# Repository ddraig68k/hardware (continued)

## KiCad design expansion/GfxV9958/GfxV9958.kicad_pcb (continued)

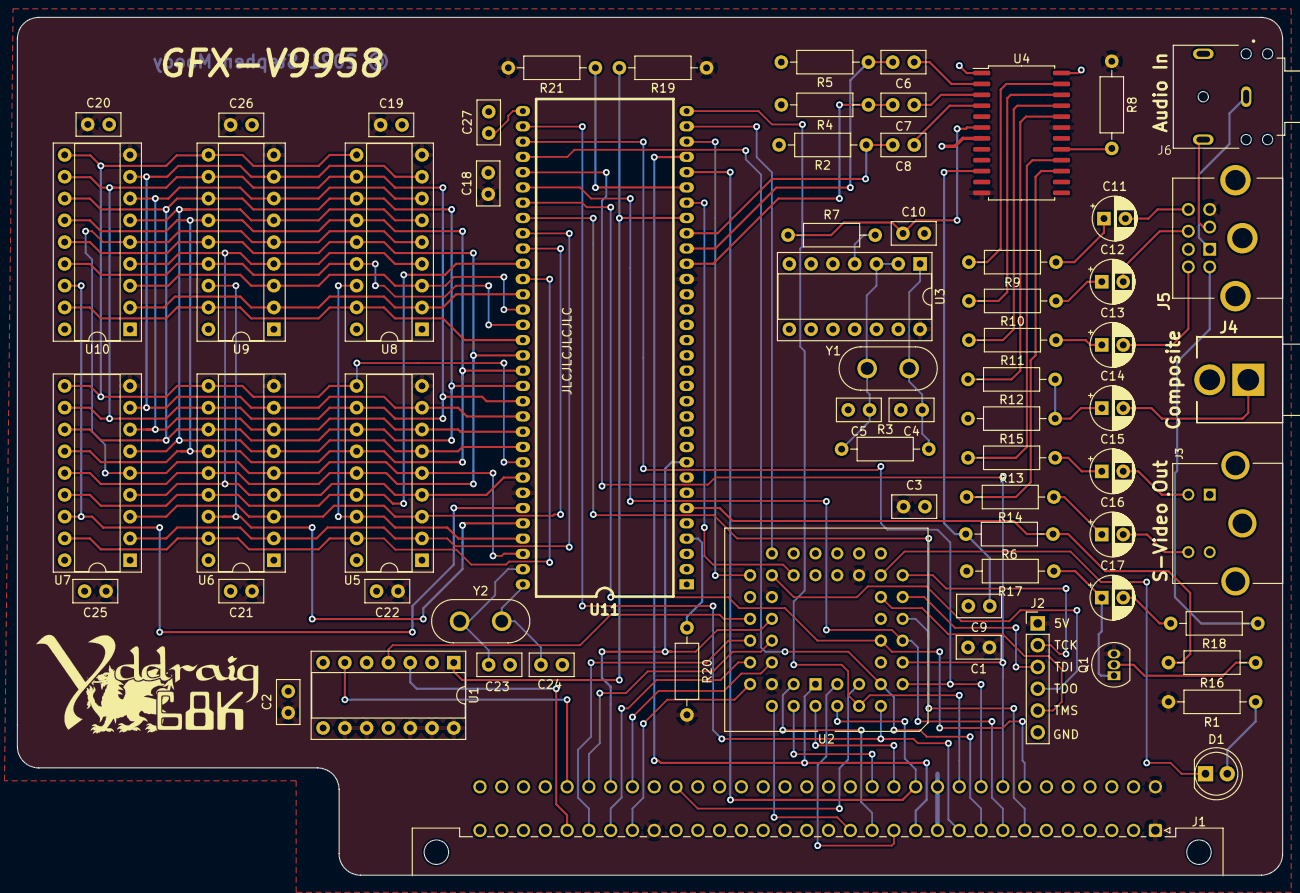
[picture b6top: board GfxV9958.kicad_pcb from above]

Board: 2 copper layers, 147.5 x 100.0 mm, 69 parts (0 on the bottom side), 100 nets.

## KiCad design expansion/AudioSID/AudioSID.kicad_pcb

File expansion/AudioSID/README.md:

# Dual SID Audio Card

The [MOS 6581/8580 SID](https://en.wikipedia.org/wiki/MOS_Technology_SID) is the sound chip used in the Commodore 64, with 3 independent oscillators, multiple waveforms, ADSR envelopes and a multi-mode filter giving it its distinctive sound.

This card has two SID sockets, each jumper-selectable between the original 6581 and the later 8580 variant, since the two chips have different characteristics - the 8580 cleaned up some of the 6581's non-linearities and runs from a 9V analog supply rather than the 6581's 12V. The board provides both rails, with an L7809 regulator supplying the 9V needed by the 8580.

A Xilinx XC9536PC44 CPLD handles address decoding and chip select generation for both SID sockets. Each SID has its own volume potentiometer for mixing before the two channels are combined into a single audio output, with a separate analog supply and ground plane to help keep noise out of the signal.

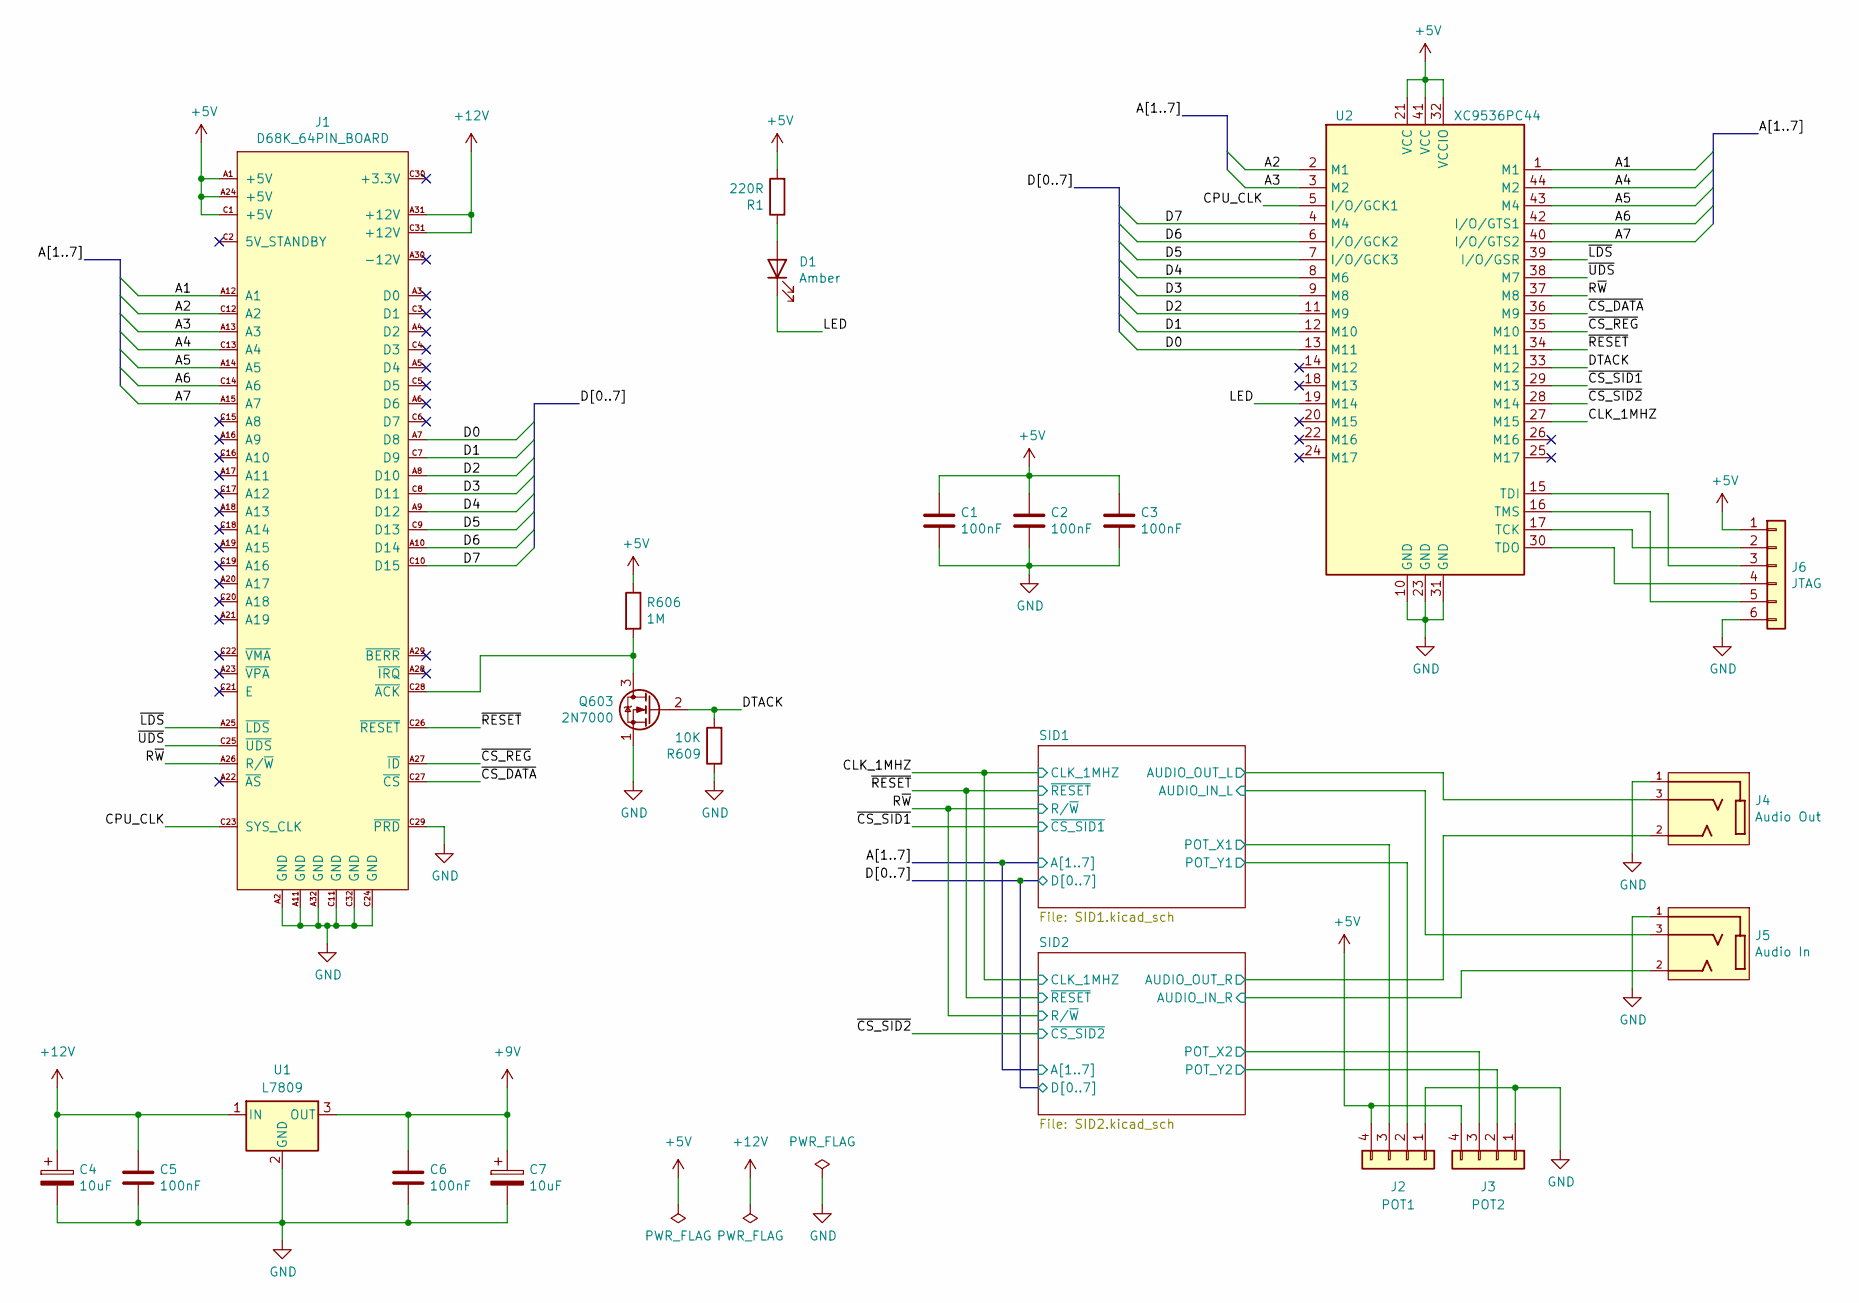
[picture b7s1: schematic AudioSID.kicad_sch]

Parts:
C1, C2, C3, C5, C6: 100nF; C_Disc_D5.0mm_W2.5mm_P2.50mm
C4, C7: 10uF; CP_Radial_D5.0mm_P2.50mm
D1: Amber; LED_D5.0mm
J1: D68K_64PIN_BOARD; DIN41612_C_2x32_Male_Horizontal_THT
J2: POT1; PinHeader_1x04_P2.54mm_Vertical
J3: POT2; PinHeader_1x04_P2.54mm_Vertical
J4: Audio Out; SWITCHCRAFT_35RAPC2BHN2; PARTREV L
J5: Audio In; SWITCHCRAFT_35RAPC2BHN2; PARTREV L
J6: JTAG; PinHeader_1x06_P2.54mm_Vertical
Q603: 2N7000; TO-92_Inline
R1: 220R; R_Axial_DIN0207_L6.3mm_D2.5mm_P10.16mm_Horizontal
R606: 1M; R_Axial_DIN0207_L6.3mm_D2.5mm_P10.16mm_Horizontal
R609: 10K; R_Axial_DIN0207_L6.3mm_D2.5mm_P10.16mm_Horizontal
U1: L7809; TO-220-3_Horizontal_TabDown
U2: XC9536PC44; PLCC-44_THT-Socket

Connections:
/A1: J1.A12 (A1), U2.1 (M1); also elsewhere on the board
/A2: J1.C12 (A2), U2.2 (M1); also elsewhere on the board
/A3: J1.A13 (A3), U2.3 (M2); also elsewhere on the board
/A4: J1.C13 (A4), U2.44 (M2); also elsewhere on the board
/A5: J1.A14 (A5), U2.43 (M4); also elsewhere on the board
/A6: J1.C14 (A6), U2.42 (I/O/GTS1)
/A7: J1.A15 (A7), U2.40 (I/O/GTS2)
/CLK_1MHZ: U2.27 (M15); also elsewhere on the board
/CPU_CLK: J1.C23 (SYS_CLK), U2.5 (I/O/GCK1)
/D0: J1.A7 (D8), U2.13 (M11); also elsewhere on the board
/D1: J1.C7 (D9), U2.12 (M10); also elsewhere on the board
/D2: J1.A8 (D10), U2.11 (M9); also elsewhere on the board
/D3: J1.C8 (D11), U2.9 (M8); also elsewhere on the board
/D4: J1.A9 (D12), U2.8 (M6); also elsewhere on the board
/D5: J1.C9 (D13), U2.7 (I/O/GCK3); also elsewhere on the board
/D6: J1.A10 (D14), U2.6 (I/O/GCK2); also elsewhere on the board
/D7: J1.C10 (D15), U2.4 (M4); also elsewhere on the board
/DTACK: U2.33 (M12); also elsewhere on the board
/LED: D1.1 (K), U2.19 (M14)
/R~W: J1.A26 (R/~W), U2.37 (M8); also elsewhere on the board
/SID1/AUDIO_IN_L: J5.3; also elsewhere on the board
/SID1/AUDIO_OUT_L: J4.3; also elsewhere on the board
/SID1/POT_Y1: J2.2; also elsewhere on the board
/SID2/AUDIO_IN_R: J5.2; also elsewhere on the board
/SID2/AUDIO_OUT_R: J4.2; also elsewhere on the board
/SID2/POT_X2: J3.3; also elsewhere on the board
/SID2/POT_Y2: J3.2; also elsewhere on the board
/~CS_DATA: J1.C27 (~CS), U2.36 (M9)
/~CS_REG: J1.A27 (~ID), U2.35 (M10)
/~CS_SID1: U2.29 (M13); also elsewhere on the board
/~CS_SID2: U2.28 (M14); also elsewhere on the board
/~LDS: J1.A25 (~LDS), U2.39 (I/O/GSR)
/~RESET: J1.C26 (~RESET), U2.34 (M11); also elsewhere on the board
/~UDS: J1.C25 (~UDS), U2.38 (M7)
GND: C1.2, C2.2, C3.2, C4.2, C5.2, C6.2, C7.2, J1.A2 (GND), J1.A11 (GND), J1.A32 (GND), J1.C11 (GND), J1.C24 (GND), J1.C29 (~PRD), J1.C32 (GND), J2.1, J3.1, J4.1, J5.1, J6.6, U1.2 (GND), U2.10 (GND), U2.23 (GND), U2.31 (GND); also elsewhere on the board
unnamed: D1.2 (A), R1.1
unnamed 36: J1.C28 (~ACK); also elsewhere on the board
unnamed: J6.2, U2.17 (TCK)
unnamed: J6.3, U2.15 (TDI)
unnamed: J6.4, U2.30 (TDO)
unnamed: J6.5, U2.16 (TMS)

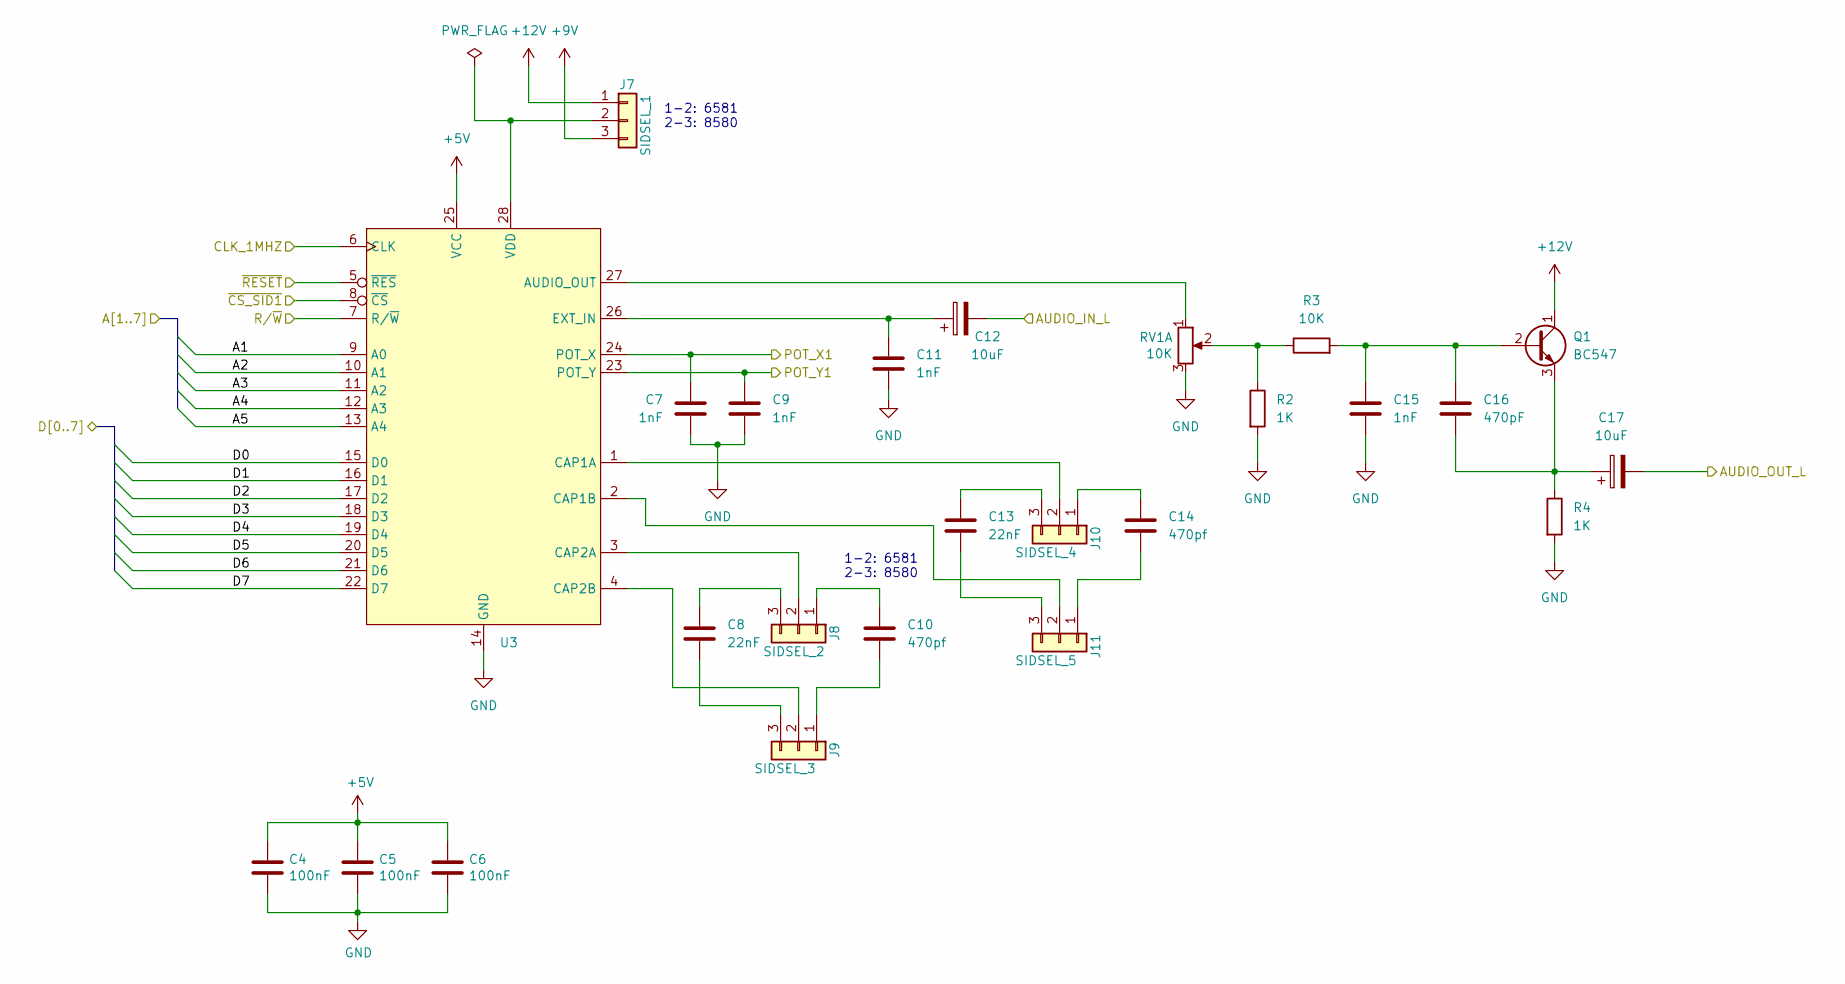
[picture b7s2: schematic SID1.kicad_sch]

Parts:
C4, C5, C6: 100nF; C_Disc_D5.0mm_W2.5mm_P2.50mm
C7, C9, C11, C15: 1nF; C_Disc_D5.0mm_W2.5mm_P2.50mm
C8, C13: 22nF; C_Disc_D5.0mm_W2.5mm_P2.50mm
C10, C14: 470pf; C_Disc_D5.0mm_W2.5mm_P2.50mm
C12, C17: 10uF; CP_Radial_D5.0mm_P2.50mm
C16: 470pF; C_Disc_D5.0mm_W2.5mm_P2.50mm
J7: SIDSEL_1; PinHeader_1x03_P2.54mm_Vertical
J8: SIDSEL_2; PinHeader_1x03_P2.54mm_Vertical
J9: SIDSEL_3; PinHeader_1x03_P2.54mm_Vertical
J10: SIDSEL_4; PinHeader_1x03_P2.54mm_Vertical
J11: SIDSEL_5; PinHeader_1x03_P2.54mm_Vertical
Q1: BC547; TO-92_Inline
R2, R4: 1K; R_Axial_DIN0207_L6.3mm_D2.5mm_P10.16mm_Horizontal
R3: 10K; R_Axial_DIN0207_L6.3mm_D2.5mm_P10.16mm_Horizontal
RV1: 10K; Potentiometer_Alps_RK163_Dual_Horizontal
U3: DIP-28_W15.24mm_Socket

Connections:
/A1: U3.9 (A0); also elsewhere on the board
/A2: U3.10 (A1); also elsewhere on the board
/A3: U3.11 (A2); also elsewhere on the board
/A4: U3.12 (A3); also elsewhere on the board
/A5: U3.13 (A4); also elsewhere on the board
/CLK_1MHZ: U3.6 (CLK); also elsewhere on the board
/D0: U3.15 (D0); also elsewhere on the board
/D1: U3.16 (D1); also elsewhere on the board
/D2: U3.17 (D2); also elsewhere on the board
/D3: U3.18 (D3); also elsewhere on the board
/D4: U3.19 (D4); also elsewhere on the board
/D5: U3.20 (D5); also elsewhere on the board
/D6: U3.21 (D6); also elsewhere on the board
/D7: U3.22 (D7); also elsewhere on the board
/R~W: U3.7 (R/~W); also elsewhere on the board
/SID1/AUDIO_IN_L: C12.2; also elsewhere on the board
/SID1/AUDIO_OUT_L: C17.2; also elsewhere on the board
/SID1/POT_Y1: C9.1, U3.23 (POT_Y); also elsewhere on the board
/~CS_SID1: U3.8 (~CS); also elsewhere on the board
/~RESET: U3.5 (~RES); also elsewhere on the board
GND: C4.2, C5.2, C6.2, C7.2, C9.2, C11.2, C15.2, R2.2, R4.2, RV1.3, U3.14 (GND); also elsewhere on the board
unnamed: J7.2, U3.28 (VDD)
unnamed: C10.1, J8.1
unnamed: J8.2, U3.3 (CAP2A)
unnamed: C8.1, J8.3
unnamed: C10.2, J9.1
unnamed: J9.2, U3.4 (CAP2B)
unnamed: C8.2, J9.3
unnamed: C14.1, J10.1
unnamed: J10.2, U3.1 (CAP1A)
unnamed: C13.1, J10.3
unnamed: C14.2, J11.1
unnamed: J11.2, U3.2 (CAP1B)
unnamed: C13.2, J11.3
unnamed: C15.1, C16.1, Q1.2 (B), R3.2
unnamed: C16.2, C17.1, Q1.3 (E), R4.1
unnamed: R2.1, R3.1, RV1.2
unnamed: RV1.1, U3.27 (AUDIO_OUT)
unnamed: C11.1, C12.1, U3.26 (EXT_IN)

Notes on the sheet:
1-2: 6581 2-3: 8580

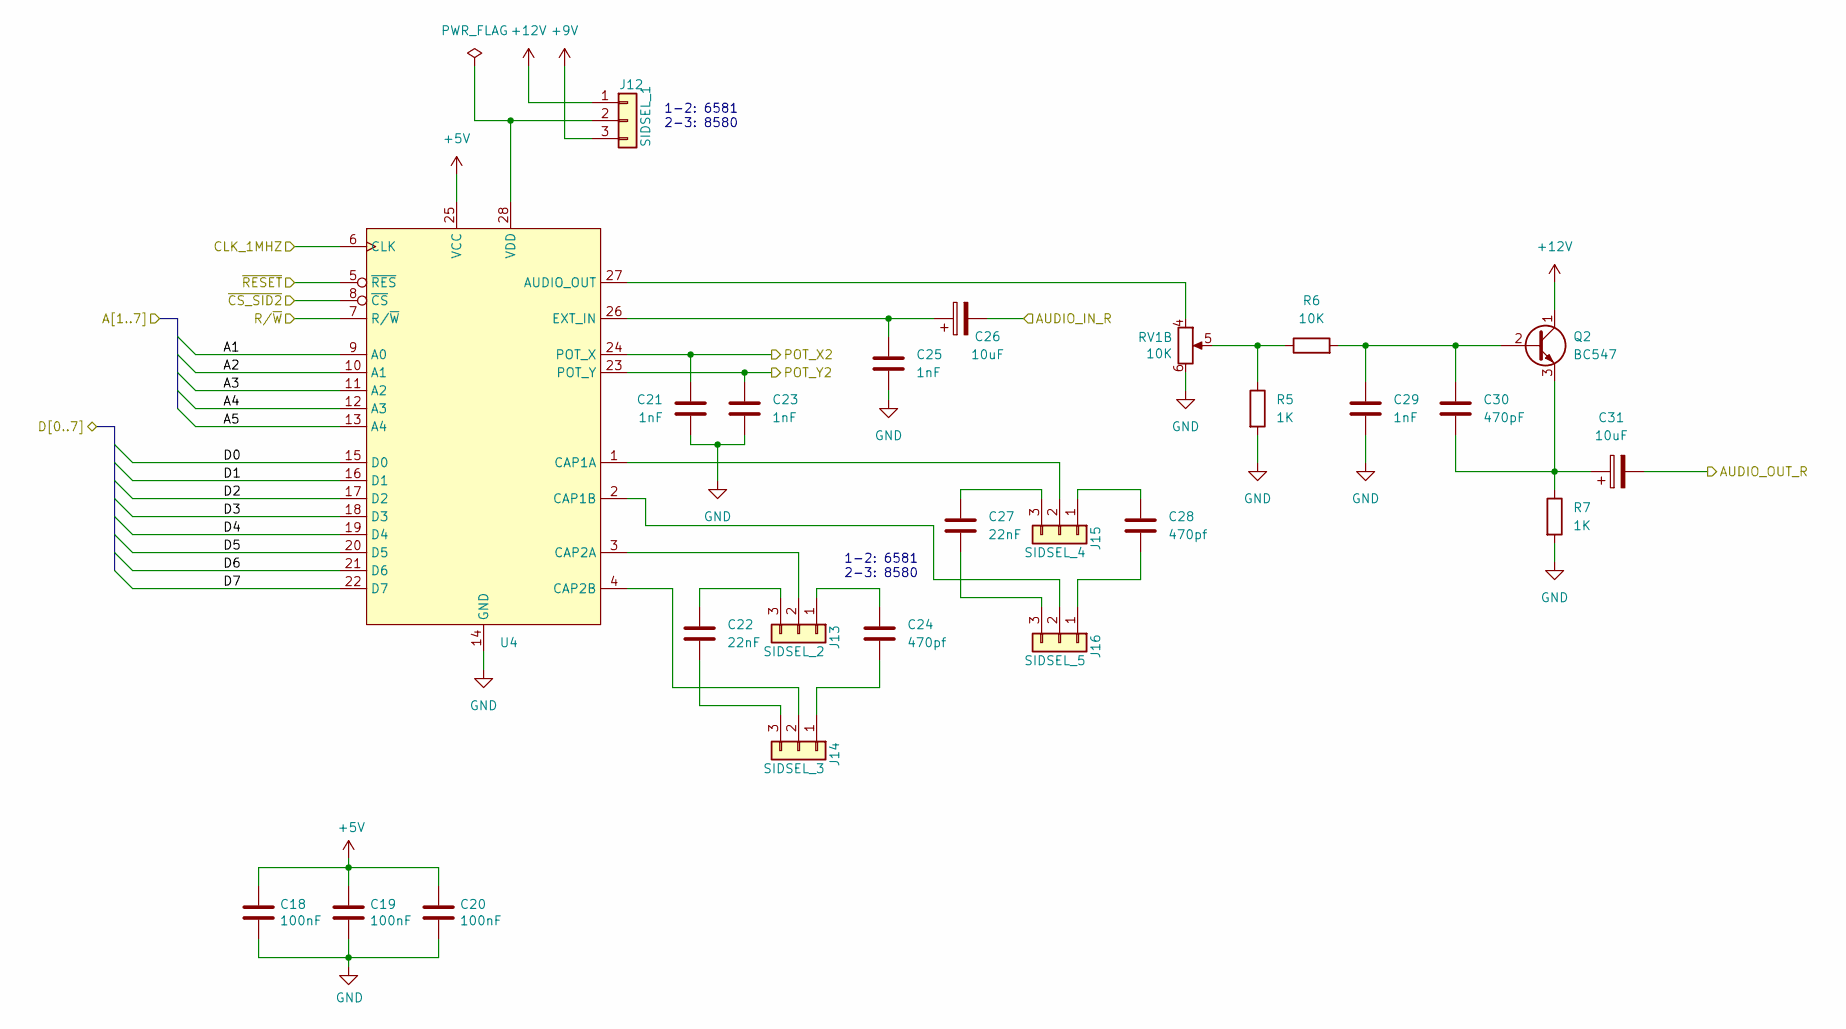
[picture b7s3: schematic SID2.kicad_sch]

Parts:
C18, C19, C20: 100nF; C_Disc_D5.0mm_W2.5mm_P2.50mm
C21, C23, C25, C29: 1nF; C_Disc_D5.0mm_W2.5mm_P2.50mm
C22, C27: 22nF; C_Disc_D5.0mm_W2.5mm_P2.50mm
C24, C28: 470pf; C_Disc_D5.0mm_W2.5mm_P2.50mm
C26, C31: 10uF; CP_Radial_D5.0mm_P2.50mm
C30: 470pF; C_Disc_D5.0mm_W2.5mm_P2.50mm
J12: SIDSEL_1; PinHeader_1x03_P2.54mm_Vertical
J13: SIDSEL_2; PinHeader_1x03_P2.54mm_Vertical
J14: SIDSEL_3; PinHeader_1x03_P2.54mm_Vertical
J15: SIDSEL_4; PinHeader_1x03_P2.54mm_Vertical
J16: SIDSEL_5; PinHeader_1x03_P2.54mm_Vertical
Q2: BC547; TO-92_Inline
R5, R7: 1K; R_Axial_DIN0207_L6.3mm_D2.5mm_P10.16mm_Horizontal
R6: 10K; R_Axial_DIN0207_L6.3mm_D2.5mm_P10.16mm_Horizontal
RV1: 10K; Potentiometer_Alps_RK163_Dual_Horizontal
U4: DIP-28_W15.24mm_Socket

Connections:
/A1: U4.9 (A0); also elsewhere on the board
/A2: U4.10 (A1); also elsewhere on the board
/A3: U4.11 (A2); also elsewhere on the board
/A4: U4.12 (A3); also elsewhere on the board
/A5: U4.13 (A4); also elsewhere on the board
/CLK_1MHZ: U4.6 (CLK); also elsewhere on the board
/D0: U4.15 (D0); also elsewhere on the board
/D1: U4.16 (D1); also elsewhere on the board
/D2: U4.17 (D2); also elsewhere on the board
/D3: U4.18 (D3); also elsewhere on the board
/D4: U4.19 (D4); also elsewhere on the board
/D5: U4.20 (D5); also elsewhere on the board
/D6: U4.21 (D6); also elsewhere on the board
/D7: U4.22 (D7); also elsewhere on the board
/R~W: U4.7 (R/~W); also elsewhere on the board
/SID2/AUDIO_IN_R: C26.2; also elsewhere on the board
/SID2/AUDIO_OUT_R: C31.2; also elsewhere on the board
/SID2/POT_X2: C21.1, U4.24 (POT_X); also elsewhere on the board
/SID2/POT_Y2: C23.1, U4.23 (POT_Y); also elsewhere on the board
/~CS_SID2: U4.8 (~CS); also elsewhere on the board
/~RESET: U4.5 (~RES); also elsewhere on the board
GND: C18.2, C19.2, C20.2, C21.2, C23.2, C25.2, C29.2, R5.2, R7.2, RV1.6, U4.14 (GND); also elsewhere on the board
unnamed: J12.2, U4.28 (VDD)
unnamed: C24.1, J13.1
unnamed: J13.2, U4.3 (CAP2A)
unnamed: C22.1, J13.3
unnamed: C24.2, J14.1
unnamed: J14.2, U4.4 (CAP2B)
unnamed: C22.2, J14.3
unnamed: C28.1, J15.1
unnamed: J15.2, U4.1 (CAP1A)
unnamed: C27.1, J15.3
unnamed: C28.2, J16.1
unnamed: J16.2, U4.2 (CAP1B)
unnamed: C27.2, J16.3
unnamed: C29.1, C30.1, Q2.2 (B), R6.2
unnamed: C30.2, C31.1, Q2.3 (E), R7.1
unnamed: R5.1, R6.1, RV1.5
unnamed: RV1.4, U4.27 (AUDIO_OUT)
unnamed: C25.1, C26.1, U4.26 (EXT_IN)

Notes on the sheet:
1-2: 6581 2-3: 8580

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
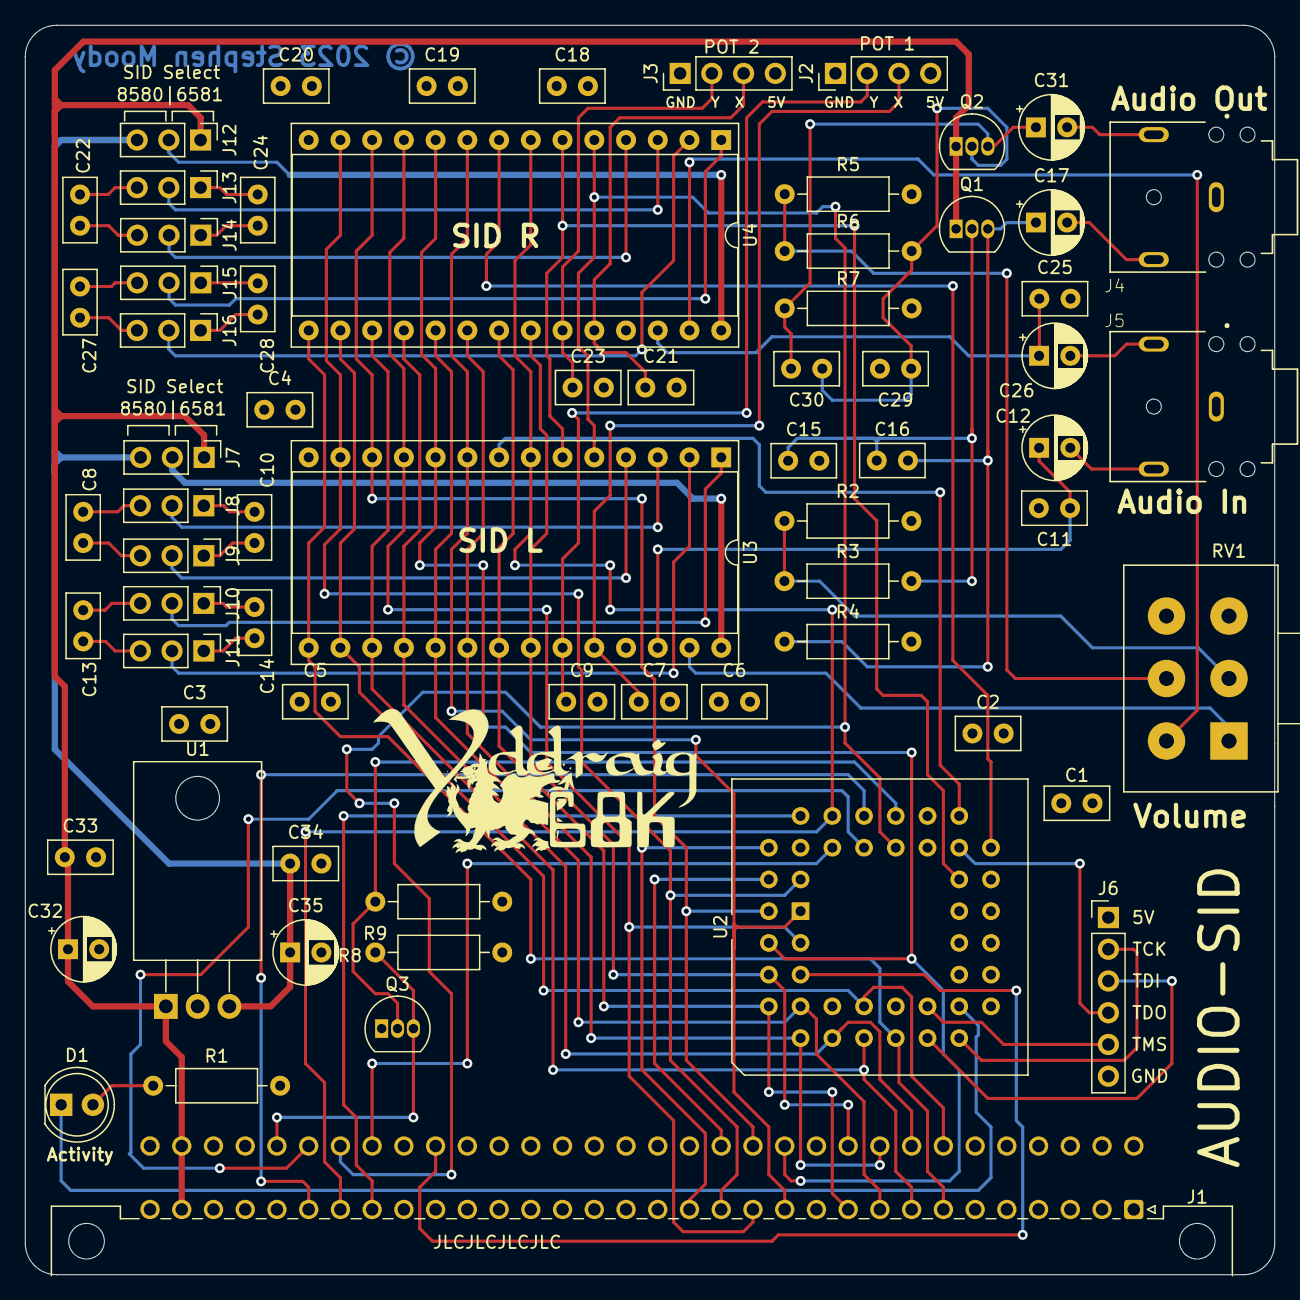
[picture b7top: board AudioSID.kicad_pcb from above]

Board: 4 copper layers, 100.0 x 100.0 mm, 69 parts (0 on the bottom side), 81 nets.

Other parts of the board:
C32, C35: 10uF; CP_Radial_D5.0mm_P2.50mm
C33, C34: 100nF; C_Disc_D5.0mm_W2.5mm_P2.50mm
Q3: 2N7000; TO-92_Inline
R8: 1M; R_Axial_DIN0207_L6.3mm_D2.5mm_P10.16mm_Horizontal
R9: 10K; R_Axial_DIN0207_L6.3mm_D2.5mm_P10.16mm_Horizontal

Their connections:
/DTACK: Q3.2 (G), R9.2; also elsewhere on the board
GND: C32.2, C33.2, C34.2, C35.2, Q3.1 (S), R9.1; also elsewhere on the board
unnamed 36: Q3.3 (D), R8.2; also elsewhere on the board

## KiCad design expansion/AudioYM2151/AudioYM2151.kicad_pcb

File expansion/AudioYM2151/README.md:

# YM2151 Sound Card

The YM2151 is a Yamaha FM synthesis chip with 8 channels, each of which has 4 operators. The YM2151 was used in many Arcade games, including games like Outrun and Ghouls 'n Ghosts.

The YM2151 has a digital output so requires a YM3012 10-bit 2-channel DAC to generate the analoge output. The output of the DAC is fed into a [TPA3122D2](https://www.ti.com/product/TPA3122D2) 15-W Amplifier.

A [LTC6903](https://www.analog.com/en/products/ltc6903.html#product-overview) 1kHz – 68MHz Programmable Oscillator is used to generate the clock for the YM2151. I chose to use a programmable oscillator here rather than a fixed frequency crystal was mainly to be able to play back VGM and other music files. Depending on the system, the frequency can be different so it could be useful to vary the clock. My music writing skills are lacking so alternative sources of music are always beneficial.

A Xilinx XC95144XL is used is used for decoding logic and as a SPI controller for the LTC6903. Although the XC95144XL is a 3.3V part, it has 5V tolerant I/O and it seems to interface with the 68000 expansion bus without issue. The 3.3V output seems to drive the 5V signals correctly so I can avoid having to add 3.3V to 5V buffers. While I wouldn't recommend this approach for a mass produced design, it seems to work on a on-off situation at least.

A quick test of playing some VGM music.

[YM2151 VGM test](https://www.youtube.com/embed/DkEkwPIz1iw)

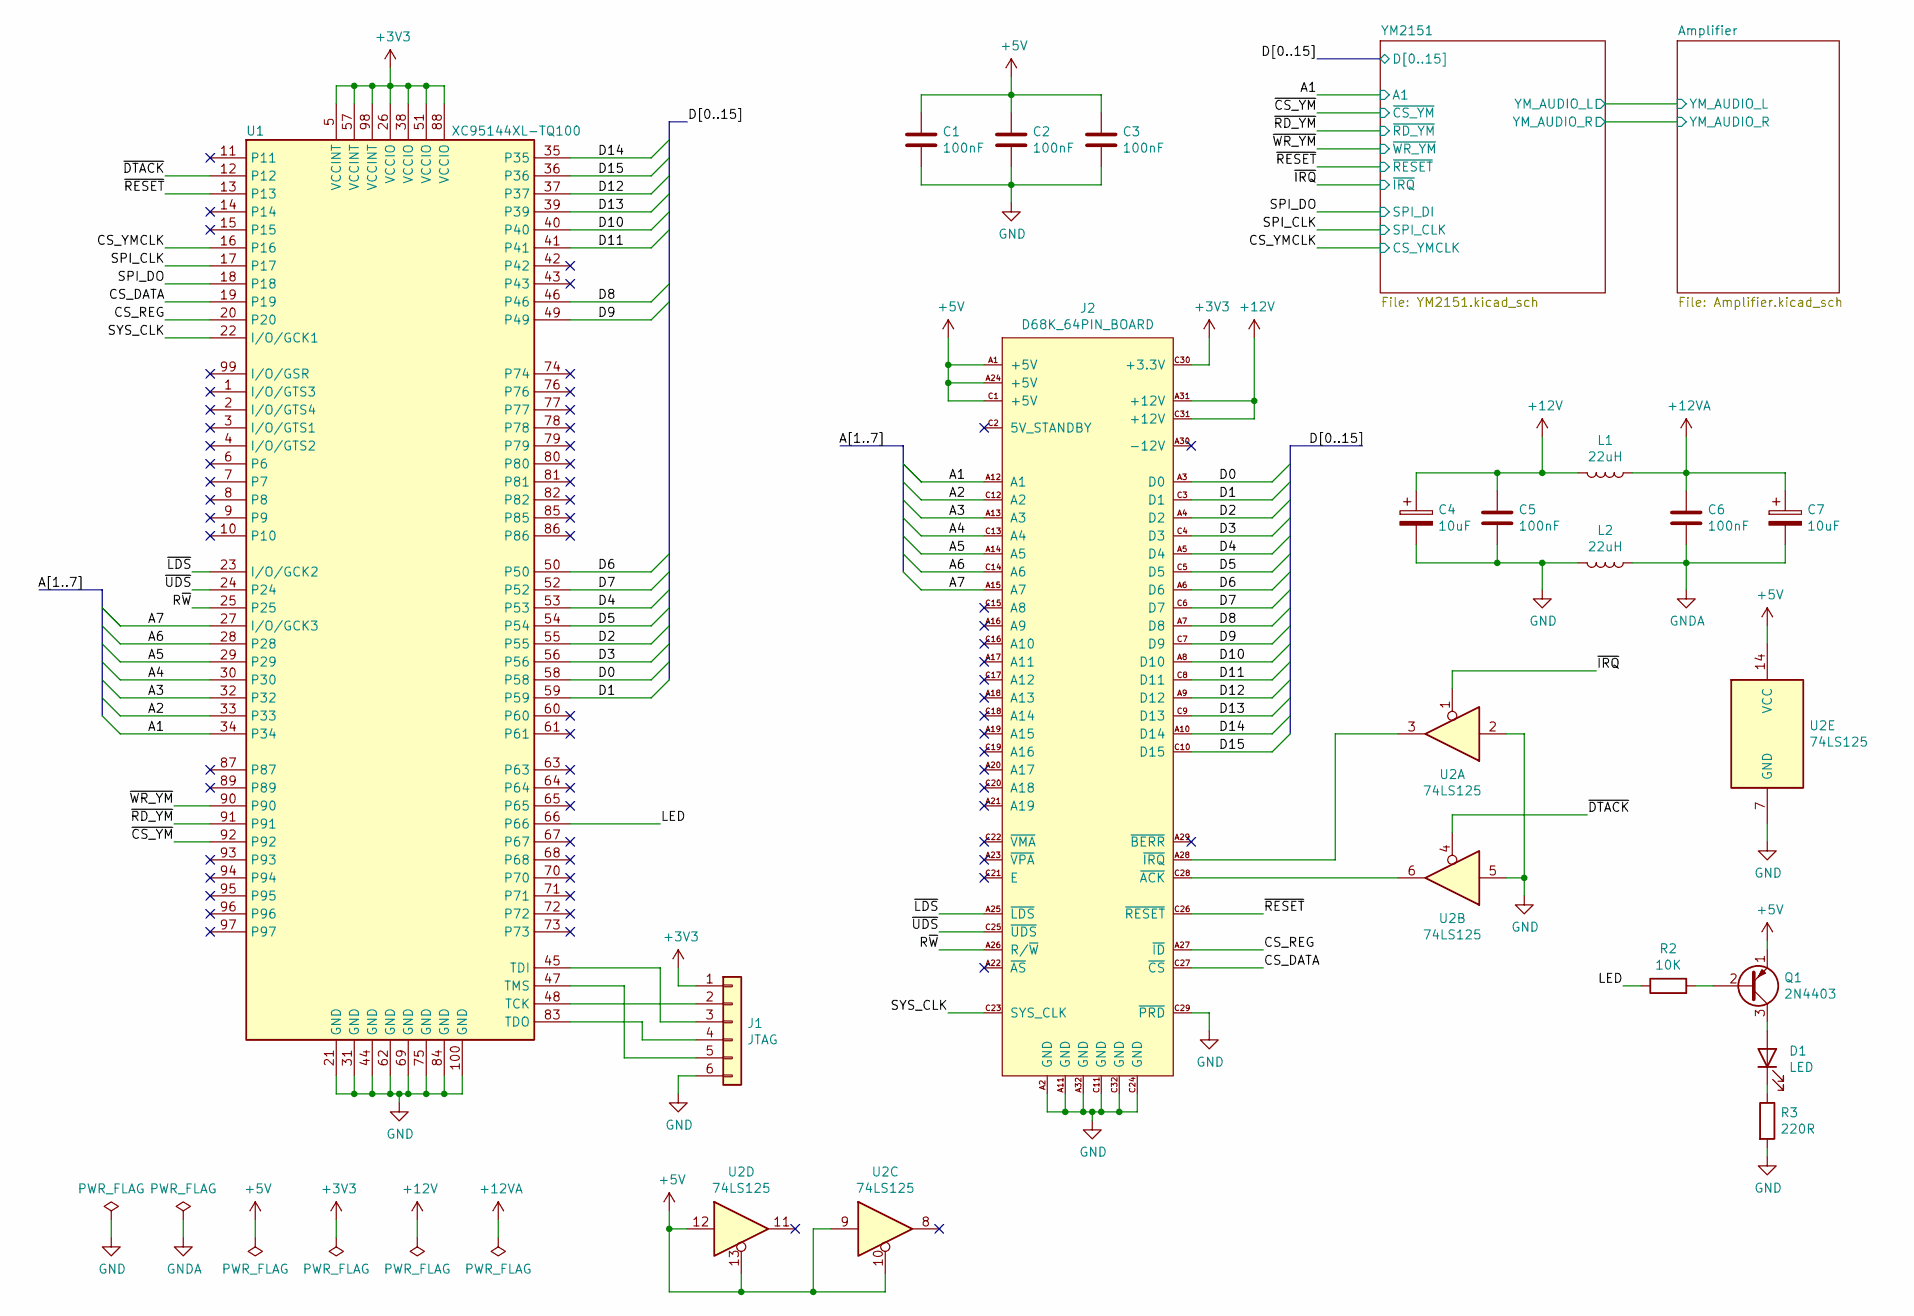
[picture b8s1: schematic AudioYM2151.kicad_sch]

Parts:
C1, C2, C3, C5, C6: 100nF; C_Disc_D5.0mm_W2.5mm_P2.50mm
C4, C7: 10uF; CP_Radial_D5.0mm_P2.50mm
D1: LED; LED_D5.0mm
J1: JTAG; PinHeader_1x06_P2.54mm_Vertical
J2: D68K_64PIN_BOARD; DIN41612_C_2x32_Male_Horizontal_THT
L1, L2: 22uH; L_Radial_D8.7mm_P5.00mm_Fastron_07HCP
Q1: 2N4403; TO-92
R2: 10K; R_Axial_DIN0207_L6.3mm_D2.5mm_P10.16mm_Horizontal
R3: 220R; R_Axial_DIN0207_L6.3mm_D2.5mm_P10.16mm_Horizontal
U1: XC95144XL-TQ100; TQFP-100_14x14mm_P0.5mm
U2: 74LS125; DIP-14_W7.62mm_Socket

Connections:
+3V3: J1.1, J2.C30 (+3.3V), U1.5 (VCCINT), U1.26 (VCCIO), U1.38 (VCCIO), U1.51 (VCCIO), U1.57 (VCCINT), U1.88 (VCCIO), U1.98 (VCCINT)
+5V: C1.1, C2.1, C3.1, J2.A1 (+5V), J2.A24 (+5V), J2.C1 (+5V), Q1.1 (E), U2.9, U2.10, U2.12, U2.13, U2.14 (VCC); also elsewhere on the board
+12V: C4.1, C5.1, J2.A31 (+12V), J2.C31 (+12V), L1.2
+12VA: C6.1, C7.1, L1.1; also elsewhere on the board
/A1: J2.A12 (A1), U1.34; also elsewhere on the board
/A2: J2.C12 (A2), U1.33
/A3: J2.A13 (A3), U1.32
/A4: J2.C13 (A4), U1.30
/A5: J2.A14 (A5), U1.29
/A6: J2.C14 (A6), U1.28
/A7: J2.A15 (A7), U1.27 (I/O/GCK3)
/CS_DATA: J2.C27 (~CS), U1.19
/CS_REG: J2.A27 (~ID), U1.20
/CS_YMCLK: U1.16; also elsewhere on the board
/D0: J2.A3 (D0), U1.58
/D1: J2.C3 (D1), U1.59
/D2: J2.A4 (D2), U1.55
/D3: J2.C4 (D3), U1.56
/D4: J2.A5 (D4), U1.53
/D5: J2.C5 (D5), U1.54
/D6: J2.A6 (D6), U1.50
/D7: J2.C6 (D7), U1.52
/D8: J2.A7 (D8), U1.46; also elsewhere on the board
/D9: J2.C7 (D9), U1.49; also elsewhere on the board
/D10: J2.A8 (D10), U1.40; also elsewhere on the board
/D11: J2.C8 (D11), U1.41; also elsewhere on the board
/D12: J2.A9 (D12), U1.37; also elsewhere on the board
/D13: J2.C9 (D13), U1.39; also elsewhere on the board
/D14: J2.A10 (D14), U1.35; also elsewhere on the board
/D15: J2.C10 (D15), U1.36; also elsewhere on the board
/LED: R2.1, U1.66
/R~W: J2.A26 (R/~W), U1.25
/SPI_CLK: U1.17; also elsewhere on the board
/SPI_DO: U1.18; also elsewhere on the board
/SYS_CLK: J2.C23 (SYS_CLK), U1.22 (I/O/GCK1)
/~CS_YM: U1.92; also elsewhere on the board
/~DTACK: U1.12, U2.4
/~IRQ: U2.1; also elsewhere on the board
/~LDS: J2.A25 (~LDS), U1.23 (I/O/GCK2)
/~RD_YM: U1.91; also elsewhere on the board
/~RESET: J2.C26 (~RESET), U1.13; also elsewhere on the board
/~UDS: J2.C25 (~UDS), U1.24
/~WR_YM: U1.90; also elsewhere on the board
GND: C1.2, C2.2, C3.2, C4.2, C5.2, J1.6, J2.A2 (GND), J2.A11 (GND), J2.A32 (GND), J2.C11 (GND), J2.C24 (GND), J2.C29 (~PRD), J2.C32 (GND), L2.2, R3.2, U1.21 (GND), U1.31 (GND), U1.44 (GND), U1.62 (GND), U1.69 (GND), U1.75 (GND), U1.84 (GND), U1.100 (GND), U2.2, U2.5, U2.7 (GND); also elsewhere on the board
GNDA: C6.2, C7.2, L2.1; also elsewhere on the board
unnamed: D1.2 (A), Q1.3 (C)
unnamed: D1.1 (K), R3.1
unnamed: J1.2, U1.48 (TCK)
unnamed: J1.3, U1.45 (TDI)
unnamed: J1.4, U1.83 (TDO)
unnamed: J1.5, U1.47 (TMS)
unnamed: J2.C28 (~ACK), U2.6
unnamed: J2.A28 (~IRQ), U2.3
unnamed: Q1.2 (B), R2.2

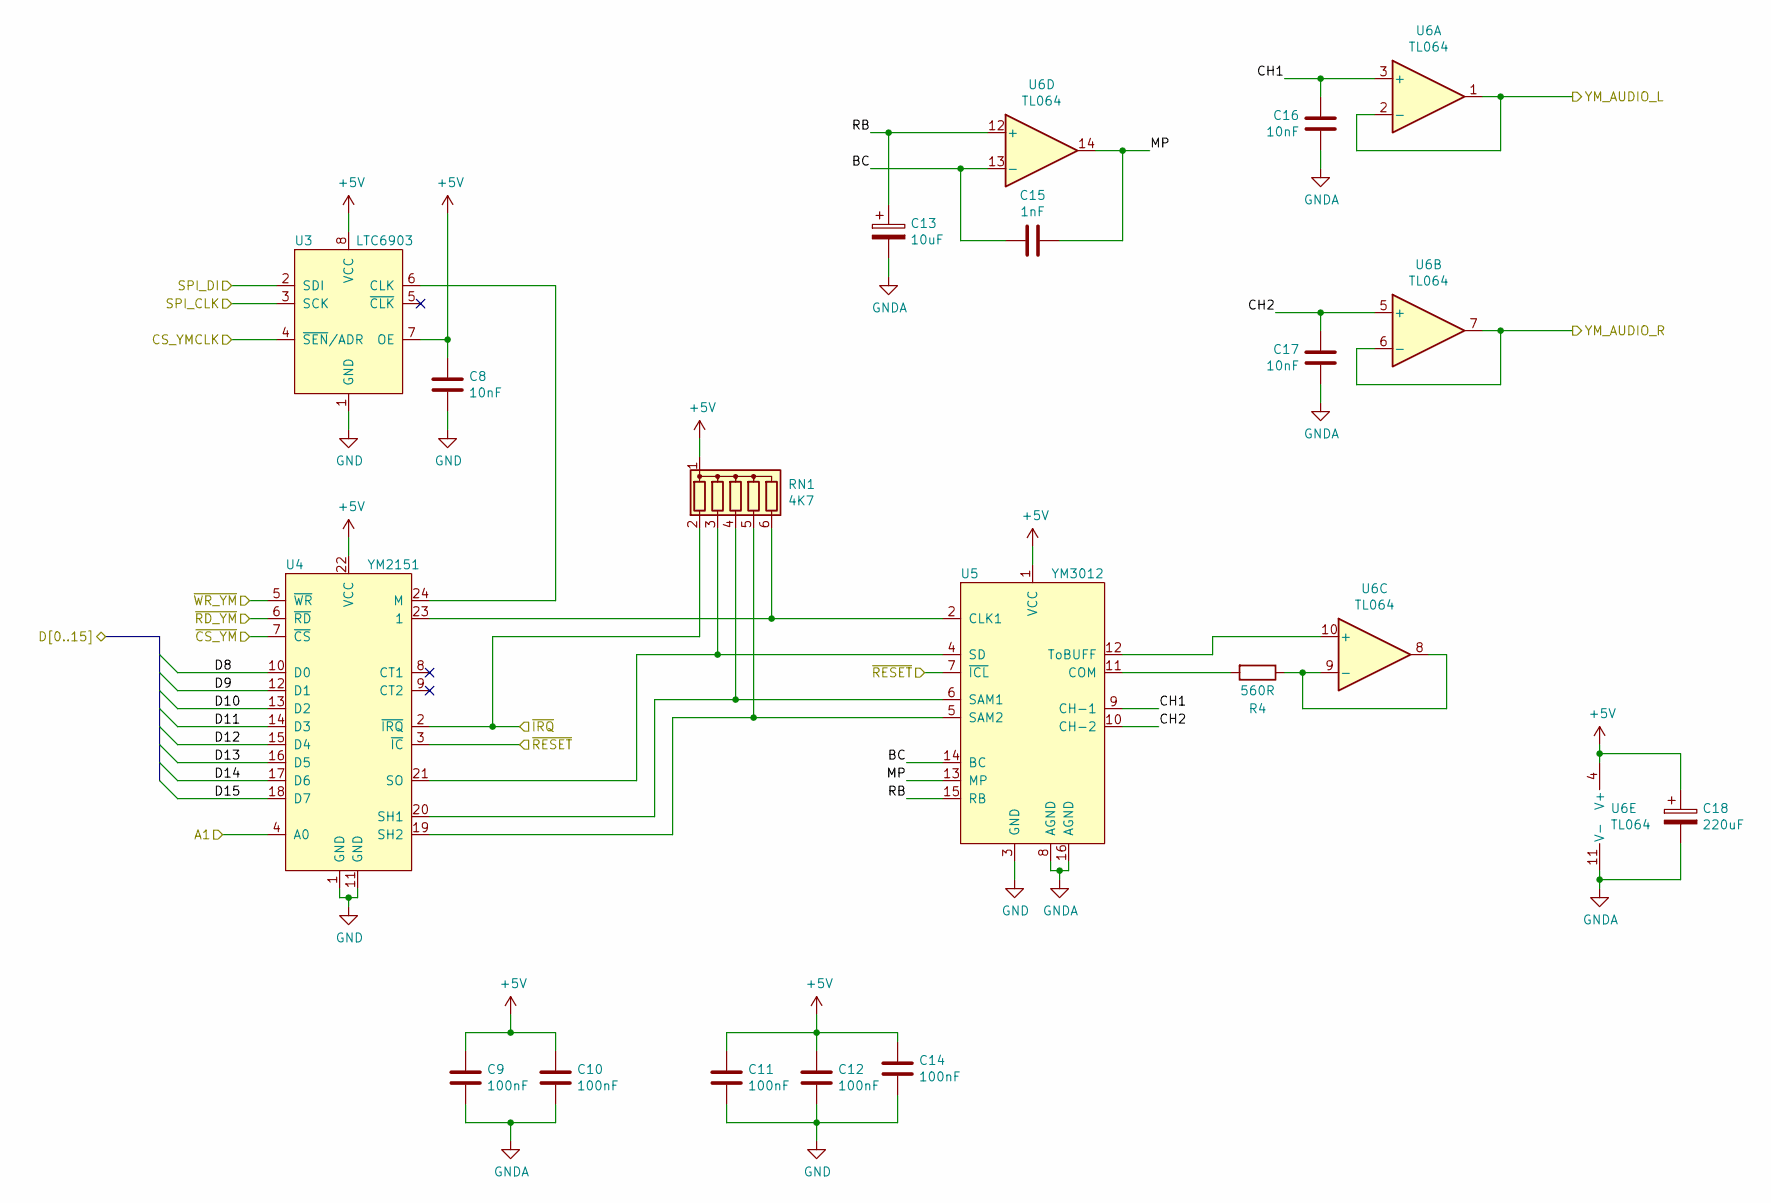
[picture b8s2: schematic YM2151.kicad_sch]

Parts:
C8, C16, C17: 10nF; C_Disc_D5.0mm_W2.5mm_P2.50mm
C9, C10, C11, C12, C14: 100nF; C_Disc_D5.0mm_W2.5mm_P2.50mm
C13: 10uF; CP_Radial_D5.0mm_P2.50mm
C15: 1nF; C_Disc_D5.0mm_W2.5mm_P2.50mm
C18: 220uF; CP_Radial_D5.0mm_P2.50mm
R4: 560R; R_Axial_DIN0207_L6.3mm_D2.5mm_P10.16mm_Horizontal
RN1: 4K7; R_Array_SIP6
U3: LTC6903; MSOP-8_3x3mm_P0.65mm
U4: YM2151; DIP-24_W15.24mm_Socket
U5: YM3012; DIP-16_W7.62mm_Socket
U6: TL064; DIP-14_W7.62mm_Socket

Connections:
+5V: C8.1, C9.1, C10.1, C11.1, C12.1, C14.1, C18.1, RN1.1 (common), U3.7 (OE), U3.8 (VCC), U4.22 (VCC), U5.1 (VCC), U6.4 (V+); also elsewhere on the board
/A1: U4.4 (A0); also elsewhere on the board
/Amplifier/YM_AUDIO_L: U6.1, U6.2 (-); also elsewhere on the board
/Amplifier/YM_AUDIO_R: U6.6 (-), U6.7; also elsewhere on the board
/CS_YMCLK: U3.4 (~SEN/ADR); also elsewhere on the board
/D8: U4.10 (D0); also elsewhere on the board
/D9: U4.12 (D1); also elsewhere on the board
/D10: U4.13 (D2); also elsewhere on the board
/D11: U4.14 (D3); also elsewhere on the board
/D12: U4.15 (D4); also elsewhere on the board
/D13: U4.16 (D5); also elsewhere on the board
/D14: U4.17 (D6); also elsewhere on the board
/D15: U4.18 (D7); also elsewhere on the board
/SPI_CLK: U3.3 (SCK); also elsewhere on the board
/SPI_DO: U3.2 (SDI); also elsewhere on the board
/YM2151/BC: C15.2, U5.14 (BC), U6.13 (-)
/YM2151/CH1: C16.2, U5.9 (CH-1), U6.3 (+)
/YM2151/CH2: C17.2, U5.10 (CH-2), U6.5 (+)
/YM2151/MP: C15.1, U5.13 (MP), U6.14
/YM2151/RB: C13.1, U5.15 (RB), U6.12 (+)
/~CS_YM: U4.7 (~CS); also elsewhere on the board
/~IRQ: RN1.2 (R1), U4.2 (~IRQ); also elsewhere on the board
/~RD_YM: U4.6 (~RD); also elsewhere on the board
/~RESET: U4.3 (~IC), U5.7 (~ICL); also elsewhere on the board
/~WR_YM: U4.5 (~WR); also elsewhere on the board
GND: C8.2, C11.2, C12.2, C14.2, U3.1 (GND), U4.1 (GND), U4.11 (GND), U5.3 (GND); also elsewhere on the board
GNDA: C9.2, C10.2, C13.2, C16.1, C17.1, C18.2, U5.8 (AGND), U5.16 (AGND), U6.11 (V-); also elsewhere on the board
unnamed: RN1.3 (R2), U4.21 (SO), U5.4 (SD)
unnamed: RN1.4 (R3), U4.20 (SH1), U5.6 (SAM1)
unnamed: RN1.5 (R4), U4.19 (SH2), U5.5 (SAM2)
unnamed: RN1.6 (R5), U4.23 (1), U5.2 (CLK1)
unnamed: U3.6 (CLK), U4.24 (M)
unnamed: R4.2, U5.11 (COM)
unnamed: U5.12 (ToBUFF), U6.10 (+)
unnamed: R4.1, U6.8, U6.9 (-)
